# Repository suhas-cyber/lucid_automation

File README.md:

# lucid_automation
# EV Lab Dashboard (Lucid proxy)
FastAPI service that serves the EV Lab HTML dashboard and aggregates:
- Lucid wall box (charger CGI via `curl`)
- Live updates over WebSocket (`/ws`)
- Optional: Pilot Dingus (USB serial), Waveshare Modbus contactors
- Optional: unified CAN/Modbus capture (`updated_log.py`) and UART logger (`uart_logger_4.py`) via `dashboard_logs.py`
## Requirements
- Python 3.11+ (3.14 OK if all deps install)
- `curl` on PATH (used for HTTPS to the charger)
- Network access to the Lucid charger and any lab SSH hosts you use for logging
## Quick start
```bash
python -m venv .venv
source .venv/bin/activate          # Windows: .venv\Scripts\activate
pip install -r requirements.txt
cd /path/to/repo
uvicorn proxy_update:app --host 0.0.0.0 --port 8000
```
### use http://host-ip:8000 from another device). host-ip is the ip of machine running uvicorn.

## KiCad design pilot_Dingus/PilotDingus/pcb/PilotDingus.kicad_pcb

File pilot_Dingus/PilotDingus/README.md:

# Getting Started
* Install VSCode https://code.visualstudio.com/download
* Within VSCode, install the PlatformIO IDE extension
* On menu bar, navigate `File > Open` and then select your clone folder of this repository
* Navigate to `src/main.cpp`
* On the toolbar at the bottom, click the checkmark ✔️ to test compile
* Attach Pilot Dingus to USB cable
* On the toolbar at the bottom, click the arrow → to test compile and upload to the microcontroller

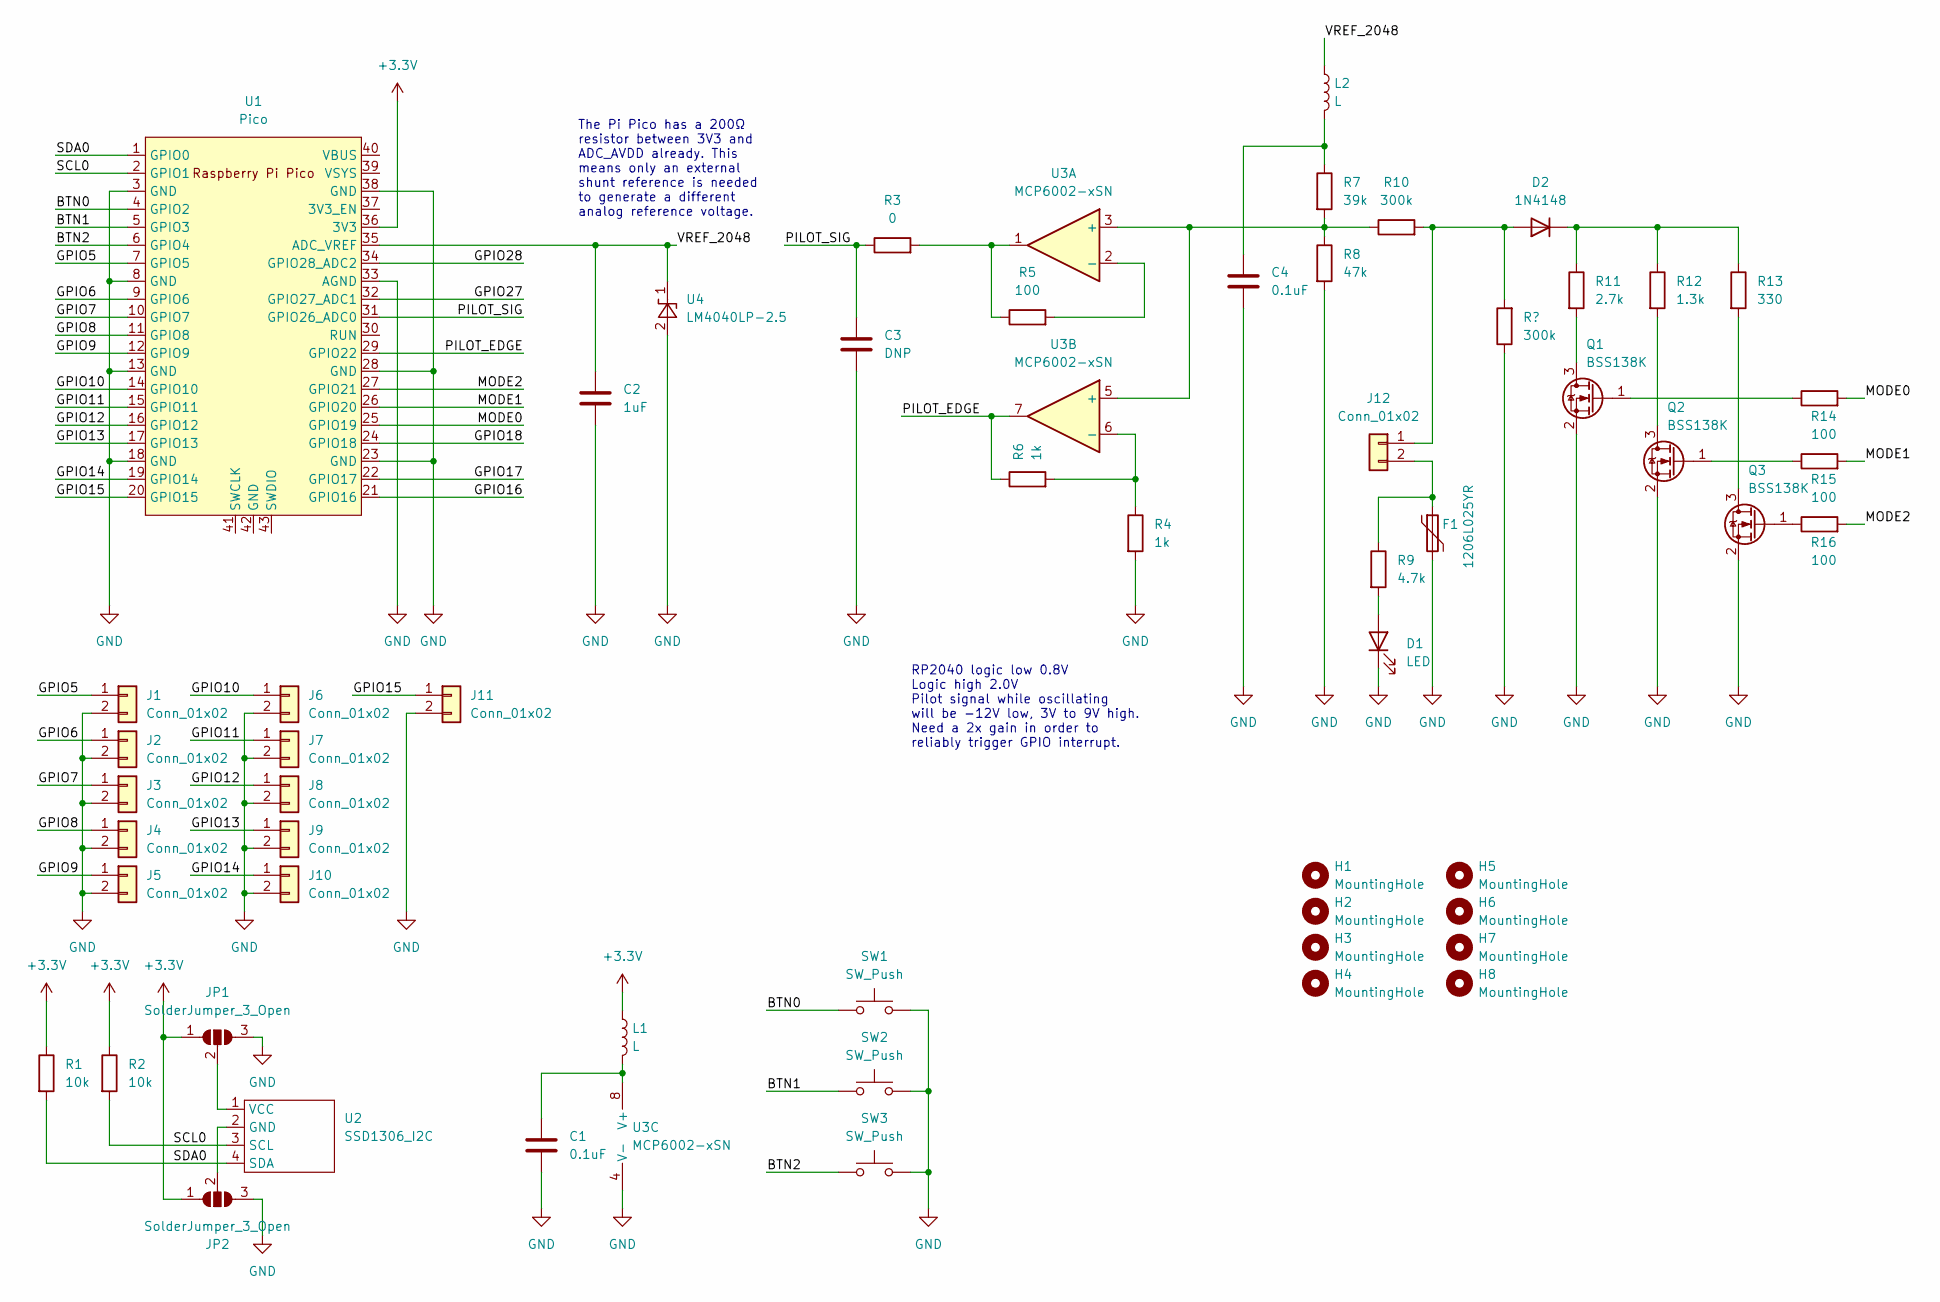
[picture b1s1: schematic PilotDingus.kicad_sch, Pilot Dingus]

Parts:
C1, C4: 0.1uF; C_0805_2012Metric
C2: 1uF; C_0805_2012Metric
C3: DNP; C_0805_2012Metric
D1: LED; LED_0805_2012Metric
D2: 1N4148; D_SOD-123
F1: 1206L025YR; Fuse_1206_3216Metric
H1, H2, H3, H4, H5, H6, H7, H8: MountingHole; MountingHole_3.2mm_M3
J1, J2, J3, J4, J5, J6, J7, J8, J9, J10, J11: Conn_01x02; PinHeader_1x02_P2.54mm_Vertical
J12: Conn_01x02; PhoenixContact_MC_1,5_2-GF-3.5_1x02_P3.50mm_Horizontal_Thre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
JP1, JP2: SolderJumper_3_Open; SolderJumper-3_P2.0mm_Open_TrianglePad1.0x1.5mm
L1, L2: L; L_0805_2012Metric
Q1, Q2, Q3: BSS138K; SOT-23
R1, R2: 10k; R_0805_2012Metric
R3: 0; R_0805_2012Metric
R4, R6: 1k; R_0805_2012Metric
R5, R14, R15, R16: 100; R_0805_2012Metric
R7: 39k; R_0805_2012Metric
R8: 47k; R_0805_2012Metric
R9: 4.7k; R_0805_2012Metric
R10: 300k; R_0805_2012Metric
R11: 2.7k; R_0805_2012Metric
R12: 1.3k; R_0805_2012Metric
R13: 330; R_0805_2012Metric
SW1, SW2, SW3: SW_Push; SW_Tactile_SPST_Angled_PTS645Vx39-2LFS
U1: Pico; RPi_Pico_SMD_TH
U2: SSD1306_I2C; SSD1306_I2C_096
U3: MCP6002-xSN; SOIC-8_3.9x4.9mm_P1.27mm
U4: LM4040LP-2.5; SOT-23

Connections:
+3.3V: JP1.1 (A), JP2.1 (A), L1.1, R1.1, R2.1, U1.36 (3V3)
/BTN0: SW1.1, U1.4 (GPIO2)
/BTN1: SW2.1, U1.5 (GPIO3)
/BTN2: SW3.1, U1.6 (GPIO4)
/GPIO5: J1.1, U1.7 (GPIO5)
/GPIO6: J2.1, U1.9 (GPIO6)
/GPIO7: J3.1, U1.10 (GPIO7)
/GPIO8: J4.1, U1.11 (GPIO8)
/GPIO9: J5.1, U1.12 (GPIO9)
/GPIO10: J6.1, U1.14 (GPIO10)
/GPIO11: J7.1, U1.15 (GPIO11)
/GPIO12: J8.1, U1.16 (GPIO12)
/GPIO13: J9.1, U1.17 (GPIO13)
/GPIO14: J10.1, U1.19 (GPIO14)
/GPIO15: J11.1, U1.20 (GPIO15)
/GPIO16: U1.21 (GPIO16)
/GPIO17: U1.22 (GPIO17)
/GPIO18: U1.24 (GPIO18)
/GPIO27: U1.32 (GPIO27_ADC1)
/GPIO28: U1.34 (GPIO28_ADC2)
/MODE0: R14.2, U1.25 (GPIO19)
/MODE1: R15.2, U1.26 (GPIO20)
/MODE2: R16.2, U1.27 (GPIO21)
/PILOT_EDGE: R6.1, U1.29 (GPIO22), U3.7
/PILOT_SIG: C3.1, R3.1, U1.31 (GPIO26_ADC0)
/SCL0: R2.2, U1.2 (GPIO1), U2.3 (SCL)
/SDA0: R1.2, U1.1 (GPIO0), U2.4 (SDA)
/VREF_2048: C2.1, L2.1, U1.35 (ADC_VREF), U4.1 (K)
GND: C1.2, C2.2, C3.2, C4.2, D1.1 (K), F1.2, J1.2, J2.2, J3.2, J4.2, J5.2, J6.2, J7.2, J8.2, J9.2, J10.2, J11.2, JP1.3 (B), JP2.3 (B), Q1.2 (S), Q2.2 (S), Q3.2 (S), R4.2, R8.2, SW1.2, SW2.2, SW3.2, U1.3 (GND), U1.8 (GND), U1.13 (GND), U1.18 (GND), U1.23 (GND), U1.28 (GND), U1.33 (AGND), U1.38 (GND), U3.4 (V-), U4.2 (A)
unnamed: C1.1, L1.2, U3.8 (V+)
unnamed: C4.1, L2.2, R7.1
unnamed: D1.2 (A), R9.2
unnamed: D2.1 (K), R11.1, R12.1, R13.1
unnamed: D2.2 (A), J12.1, R10.2
unnamed: F1.1, J12.2, R9.1
unnamed: JP1.2 (C), U2.1 (VCC)
unnamed: JP2.2 (C), U2.2 (GND)
unnamed: Q1.1 (G), R14.1
unnamed: Q1.3 (D), R11.2
unnamed: Q2.1 (G), R15.1
unnamed: Q2.3 (D), R12.2
unnamed: Q3.1 (G), R16.1
unnamed: Q3.3 (D), R13.2
unnamed: R3.2, R5.1, U3.1
unnamed: R5.2, U3.2 (-)
unnamed: R4.1, R6.2, U3.6 (-)
unnamed: R7.2, R8.1, R10.1, U3.3 (+), U3.5 (+)

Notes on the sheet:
The Pi Pico has a 200Ω resistor between 3V3 and ADC_AVDD already. This means only an external shunt reference is needed to generate a different analog reference voltage.
RP2040 logic low 0.8V Logic high 2.0V Pilot signal while oscillating will be -12V low, 3V to 9V high. Need a 2x gain in order to reliably trigger GPIO interrupt.

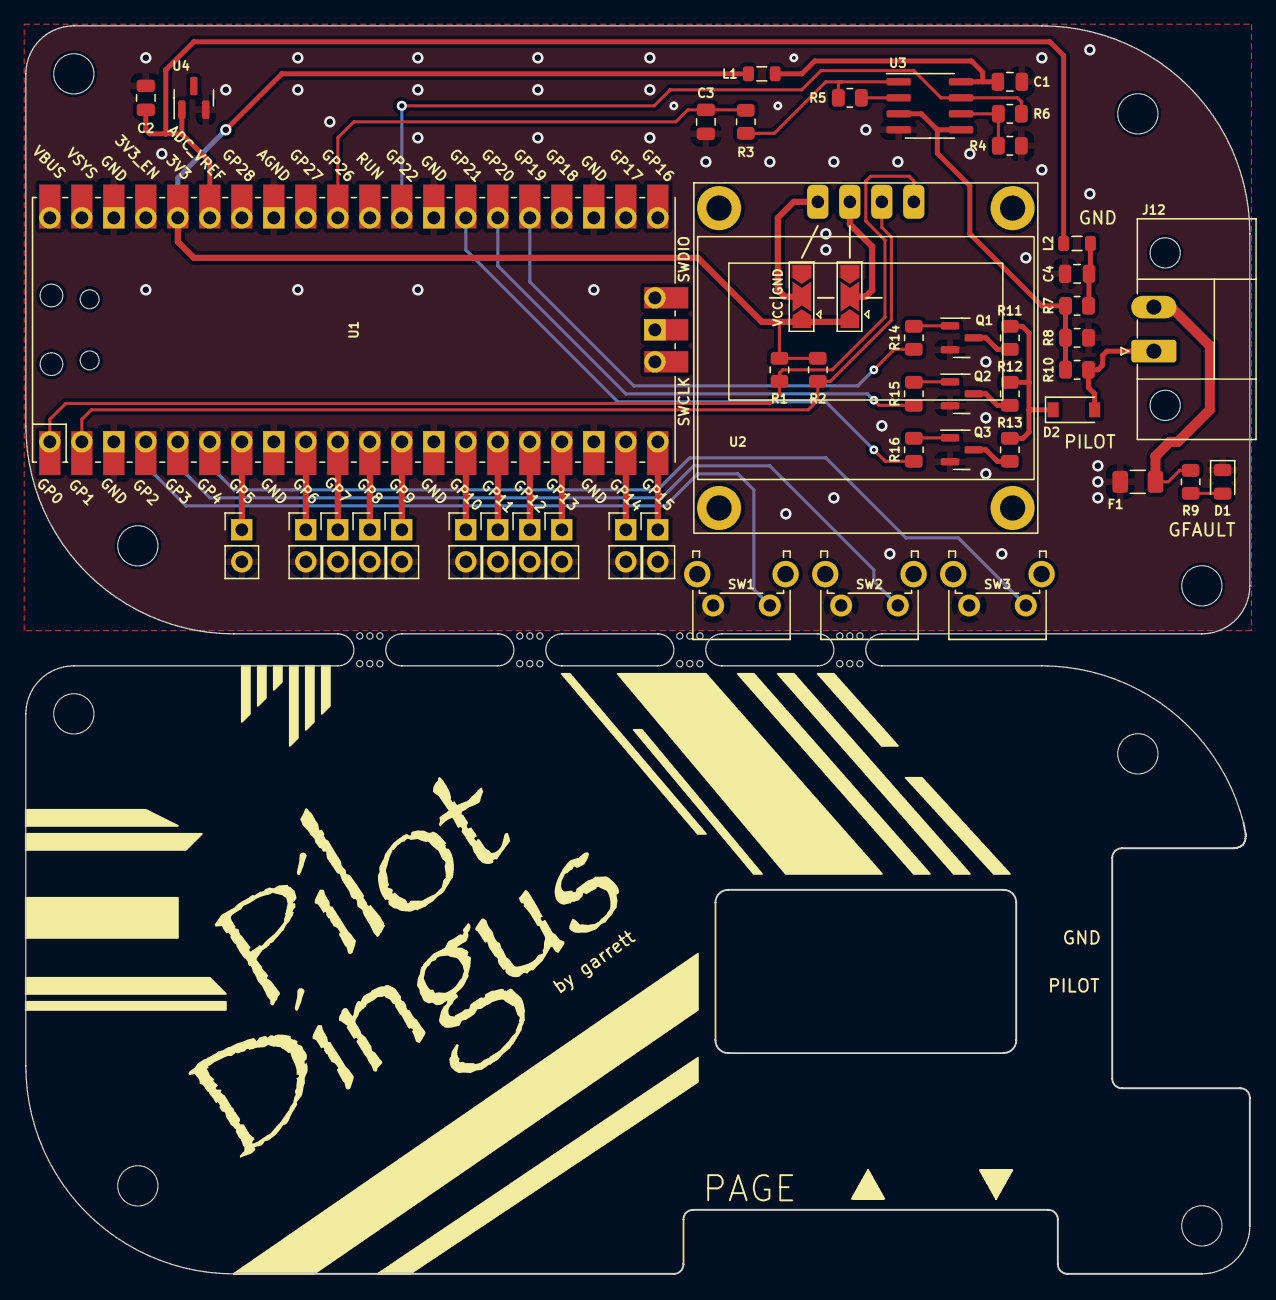
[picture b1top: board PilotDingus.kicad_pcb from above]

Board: 2 copper layers, 97.1 x 99.0 mm, 61 parts (0 on the bottom side), 42 nets.

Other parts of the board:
mouse-bite-2.54mm-slot, mouse-bite-2.54mm-slot#2, mouse-bite-2.54mm-slot#3, mouse-bite-2.54mm-slot#4: VAL**; mouse-bite-2.54mm-slot

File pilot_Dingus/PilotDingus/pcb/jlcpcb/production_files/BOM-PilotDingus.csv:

Comment,Designator,Footprint,LCSC
330,R13,R_0805_2012Metric,C105877
1k,"R4,R6",R_0805_2012Metric,C110774
1N4148,D2,D_SOD-123,C112342
2.7k,R11,R_0805_2012Metric,C114520
LM4040LP-2.0,U4,SOT-23,C131939
1.3k,R12,R_0805_2012Metric,C137582
100,"R14,R15,R16,R5",R_0805_2012Metric,C17408
10k,"R1,R2",R_0805_2012Metric,C17414
0,R3,R_0805_2012Metric,C17477
BSS138K,"Q1,Q2,Q3",SOT-23,C255592
1uF,C2,C_0805_2012Metric,C28323
300k,R10,R_0805_2012Metric,C316202
47k,R8,R_0805_2012Metric,C490805
0.1uF,"C1,C4",C_0805_2012Metric,C49678
L,"L1,L2",L_0805_2012Metric,C68035
39k,R7,R_0805_2012Metric,C706239
MCP6002-xSN,U3,SOIC-8_3.9x4.9mm_P1.27mm,C7377
1206L025YR,F1,Fuse_1206_3216Metric,

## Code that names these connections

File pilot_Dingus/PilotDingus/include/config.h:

#pragma once

#define PROTOCOL_VER 2

#define UPDATE_INTERVAL_MS 100
#define PILOT_PWM_TIMEOUT_US 5000
#define SECOND_US 1000000

#define VOLTAGE_TOLERANCE_V 1.0
#define BTN0 D2
#define BTN1 D3
#define BTN2 D4
#define MODE0 D19
#define MODE1 D20
#define MODE2 D21
#define PILOT_SIG A0
#define PILOT_EDGE D22

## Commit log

2026-04-28 Create bla
